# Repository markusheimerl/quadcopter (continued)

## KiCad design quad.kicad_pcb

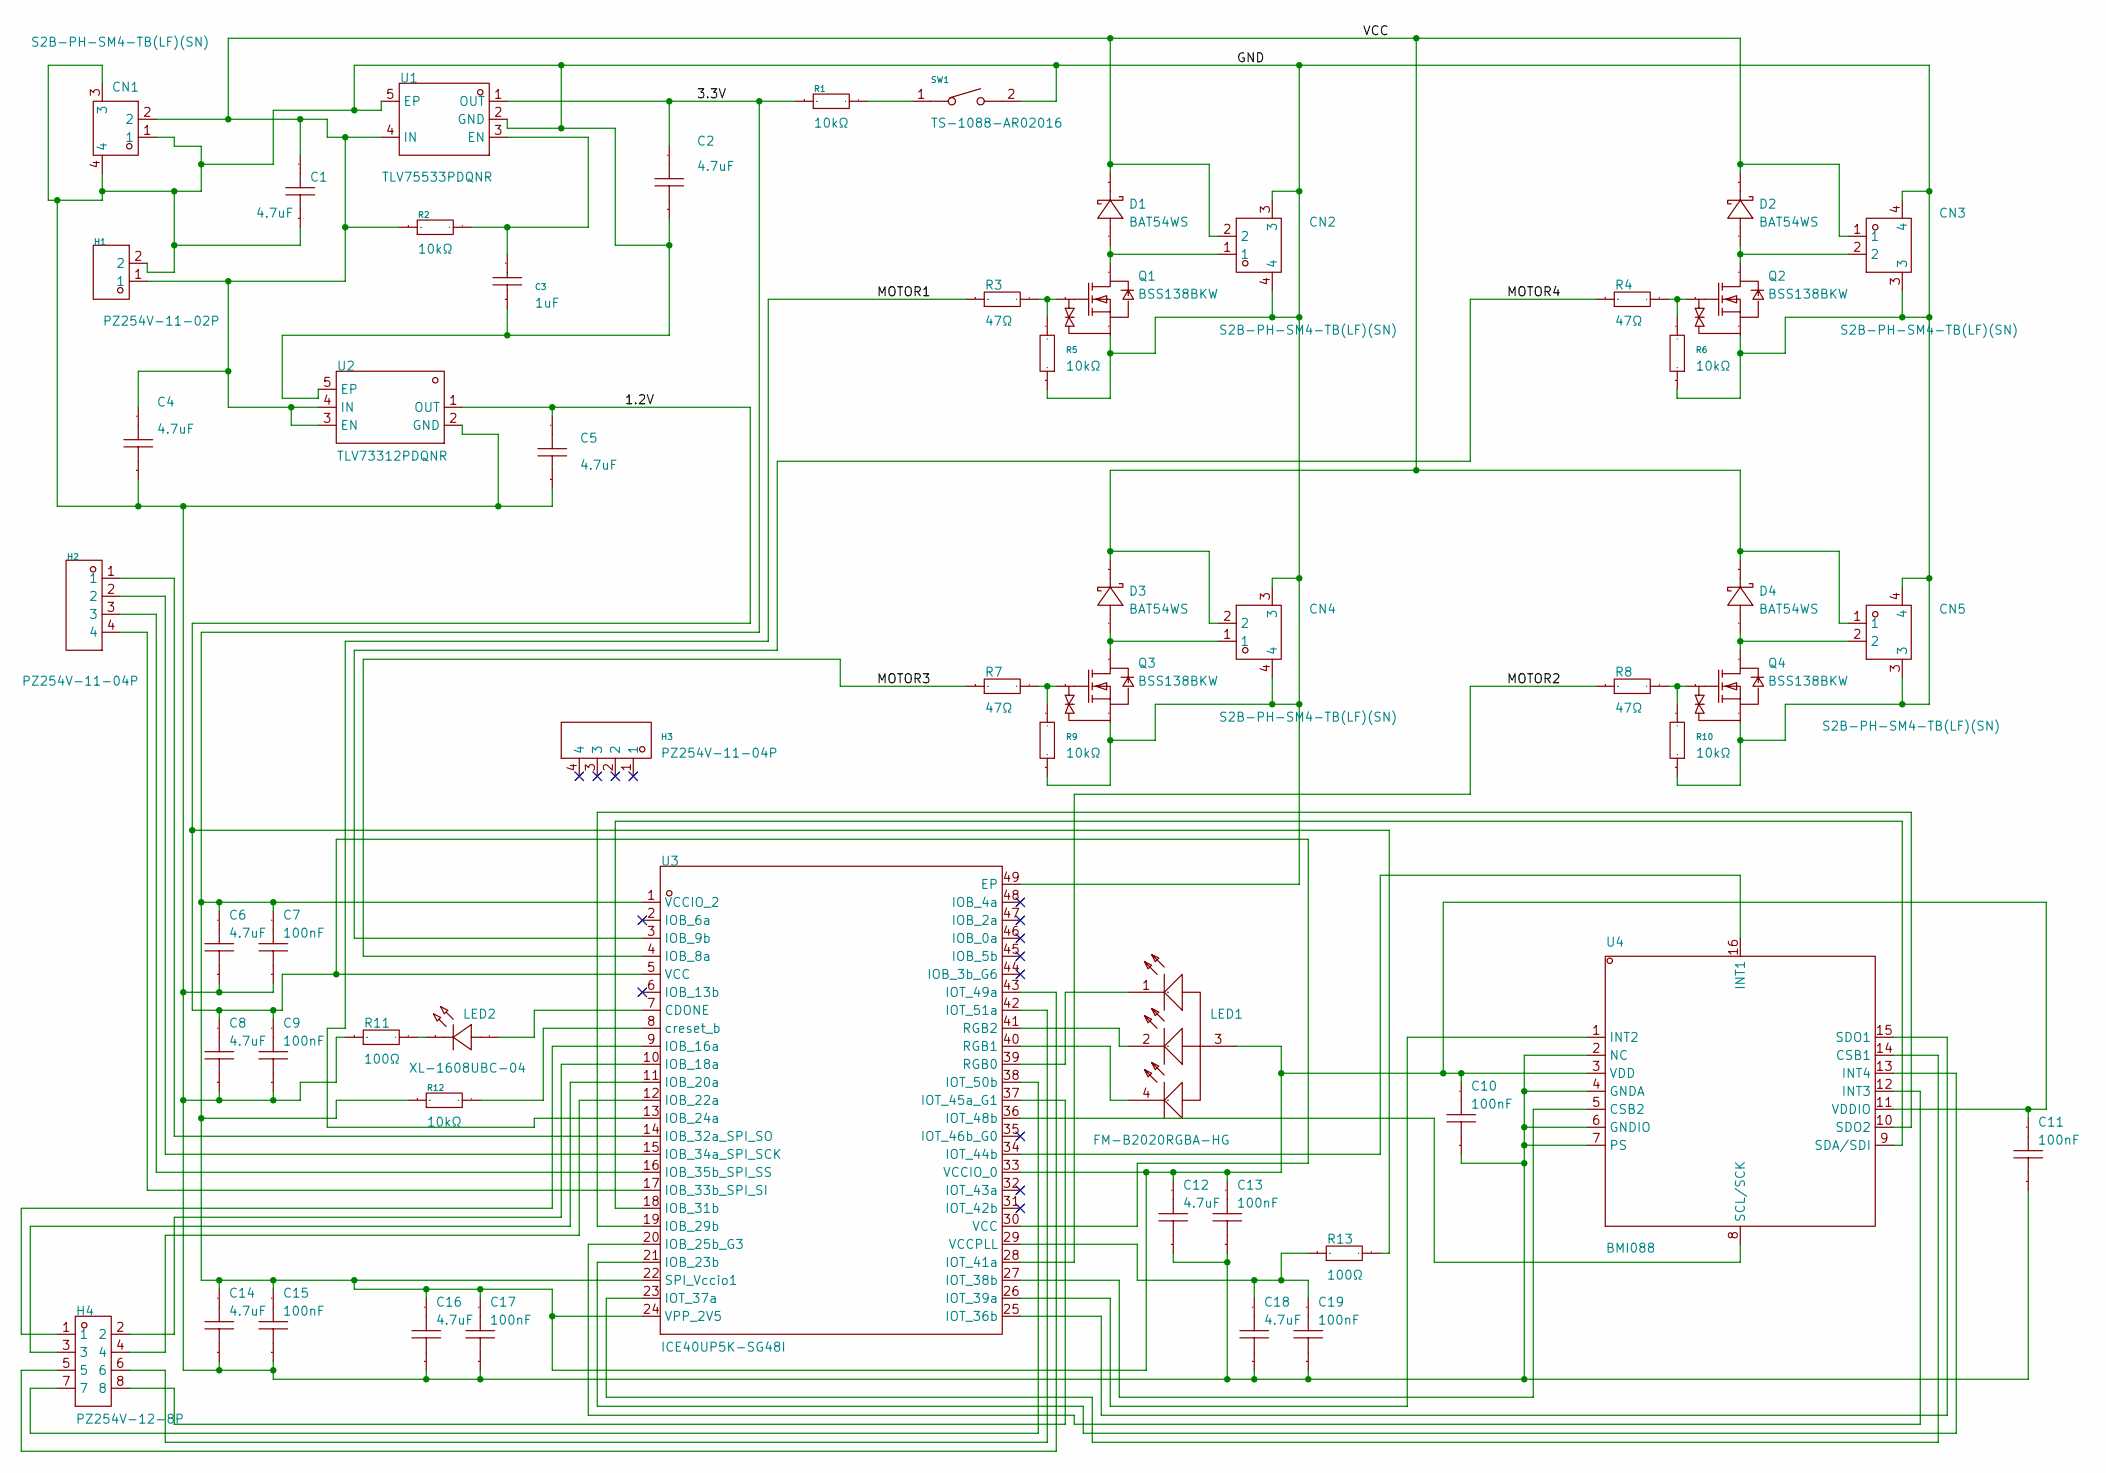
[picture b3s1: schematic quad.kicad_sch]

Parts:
C1, C2, C4, C5, C6, C8, C12, C14, C16, C18: 4.7uF; C0402; Manufacturer Part CL05A475MQ5NRNC; LCSC Part Name 4.7uF ±20% 6.3V
C3: 1uF; C0402; Manufacturer Part CL05A105KO5NNNC; LCSC Part Name 1uF ±10% 16V
C7, C9, C10, C11, C13, C15, C17, C19: 100nF; C0402; Manufacturer Part CL05B104KO5NNNC; LCSC Part Name 100nF ±10% 16V
CN1, CN2, CN3, CN4, CN5: S2B-PH-SM4-TB(LF)(SN); CONN-SMD_P2.00_S2B-PH-SM4-TB-LF-SN; Manufacturer Part S2B-PH-SM4-TB(LF)(SN); LCSC Part Name 1x2P 间距:2mm 卧贴 系列:PH
D1, D2, D3, D4: BAT54WS; SOD-323_L1.7-W1.3-LS2.6-RD-1; Manufacturer Part BAT54WS; LCSC Part Name 电压:30V 电流:200mA
H1: PZ254V-11-02P; HDR-TH_2P-P2.54-V-M; Manufacturer Part PZ254V-11-02P; LCSC Part Name 间距:2.54mm 1x2P 直插 方针
H2, H3: PZ254V-11-04P; HDR-TH_4P-P2.54-V-M; Manufacturer Part PZ254V-11-04P; LCSC Part Name 间距:2.54mm 1x4P 直插 方针
H4: PZ254V-12-8P; HDR-TH_8P-P2.54-V-M-R2-C4-S2.54; Manufacturer Part PZ254V-12-8P; LCSC Part Name 间距:2.54mm 2x4P 直插 方针
LED1: FM-B2020RGBA-HG; LED-SMD_FM-B2020RGBA-HG; Manufacturer Part FM-B2020RGBA-HG; LCSC Part Name FM-B2020RGBA-HG
LED2: XL-1608UBC-04; LED0603-RD_BLUE; Manufacturer Part XL-1608UBC-04; LCSC Part Name XL-1608UBC-04
Q1, Q2, Q3, Q4: BSS138BKW; SOT-323-3_L2.1-W1.3-P1.30-LS2.3-BL; Manufacturer Part BSS138BKW; LCSC Part Name 1个N沟道 耐压:60V 电流:300mA
R1, R2, R5, R6, R9, R10, R12: 10kΩ; R0402; Manufacturer Part 0402WGJ0103TCE; LCSC Part Name 10kΩ ±5% 62.5mW 厚膜电阻
R3, R4, R7, R8: 47Ω; R0402; Manufacturer Part RC0402FR-0747RL; LCSC Part Name 厚膜电阻 47Ω ±1% 62.5mW
R11, R13: 100Ω; R0402; Manufacturer Part RC0402FR-07100RL; LCSC Part Name 厚膜电阻 100Ω ±1% 62.5mW
SW1: TS-1088-AR02016; SW-SMD_L3.9-W3.0-P4.45; Manufacturer Part TS-1088-AR02016; LCSC Part Name 4*3*2mm 立贴 轻触开关
U1: TLV75533PDQNR; X2SON-4_L1.0-W1.0-P0.65-TL-EP; Manufacturer Part TLV75533PDQNR; LCSC Part Name 具有使能功能的 500mA、高 PSRR、低 IQ、低压降稳压器
U2: TLV73312PDQNR; X2SON-4_L1.0-W1.0-P0.65-TL-EP; Manufacturer Part TLV73312PDQNR; LCSC Part Name 具有使能功能的 300mA、低 IQ、低压降无电容稳压器
U3: ICE40UP5K-SG48I; QFN-48_L7.0-W7.0-P0.50-TL-EP5.4-1; Manufacturer Part ICE40UP5K-SG48I; LCSC Part Name ICE40UP5K SG48I
U4: BMI088; LGA-16_L4.5-W3.0-P0.50-BL; Manufacturer Part BMI088; LCSC Part Name BMI088

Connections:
1.2V: C5.2, C8.2, C9.2, R13.2, U2.1 (OUT), U3.5 (VCC), U3.30 (VCC)
3.3V: C2.2, C6.2, C7.2, C10.2, C11.2, C12.2, C13.2, C14.2, C15.2, C16.2, C17.2, LED1.3 (A), R1.1, R12.1, U1.1 (OUT), U3.1 (VCCIO_2), U3.22 (SPI_Vccio1), U3.24 (VPP_2V5), U3.33 (VCCIO_0), U4.3 (VDD), U4.11 (VDDIO)
$1N1853: C3.2, R2.2, U1.3 (EN)
$1N2745: CN3.2, D2.2 (A), Q2.3 (D)
$1N2749: Q2.1 (G), R4.2, R6.2
$1N3427: Q4.1 (G), R8.2, R10.2
$1N3454: CN5.2, D4.2 (A), Q4.3 (D)
$1N4378: CN2.1, D1.2 (A), Q1.3 (D)
$1N4400: Q1.1 (G), R3.2, R5.2
$1N4626: Q3.1 (G), R7.2, R9.2
$1N4630: CN4.1, D3.2 (A), Q3.3 (D)
$1N4970: H2.1, U3.14 (IOB_32a_SPI_SO)
$1N4976: H2.2, U3.15 (IOB_34a_SPI_SCK)
$1N4983: H2.3, U3.16 (IOB_35b_SPI_SS)
$1N5003: H2.4, U3.17 (IOB_33b_SPI_SI)
$1N7555: C18.2, C19.2, R13.1, U3.29 (VCCPLL)
$1N7780: R12.2, U3.8 (creset_b)
$1N8073: LED2.2 (A), U3.7 (CDONE)
$1N8265: LED2.1 (K), R11.2
$1N9704: LED1.2 (K), U3.41 (RGB2)
$1N9752: LED1.4 (K), U3.40 (RGB1)
$1N9758: LED1.1 (K), U3.39 (RGB0)
$1N9959: U3.25 (IOT_36b), U4.15 (SDO1)
$1N9970: U3.34 (IOT_44b), U4.16 (INT1)
$1N11822: H4.1, U3.9 (IOB_16a)
$1N11833: H4.2, U3.10 (IOB_18a)
$1N11847: H4.3, U3.11 (IOB_20a)
$1N11856: H4.4, U3.12 (IOB_22a)
$1N15818: H4.5, U3.43 (IOT_49a)
$1N15829: H4.6, U3.42 (IOT_51a)
$1N15838: H4.7, U3.38 (IOT_50b)
$1N15847: H4.8, U3.37 (IOT_45a_G1)
$1N15910: U3.18 (IOB_31b), U4.9 (SDA/SDI)
$1N15979: U3.19 (IOB_29b), U4.10 (SDO2)
$1N15998: U3.20 (IOB_25b_G3), U4.12 (INT3)
$1N16036: U3.21 (IOB_23b), U4.13 (INT4)
$1N16041: U3.27 (IOT_38b), U4.5 (CSB2)
$1N16063: U3.23 (IOT_37a), U4.14 (CSB1)
$1N16068: U3.26 (IOT_39a), U4.1 (INT2)
$1N16419: U3.36 (IOT_48b), U4.8 (SCL/SCK)
$1N18118: R1.2, SW1.1
GND: C1.1, C2.1, C3.1, C4.1, C5.1, C6.1, C7.1, C8.1, C9.1, C10.1, C11.1, C12.1, C13.1, C14.1, C15.1, C16.1, C17.1, C18.1, C19.1, CN1.1, CN1.3, CN1.4, CN2.3, CN2.4, CN3.3, CN3.4, CN4.3, CN4.4, CN5.3, CN5.4, H1.2, Q1.2 (S), Q2.2 (S), Q3.2 (S), Q4.2 (S), R5.1, R6.1, R9.1, R10.1, R11.1, SW1.2, U1.2 (GND), U1.5 (EP), U2.2 (GND), U2.5 (EP), U3.49 (EP), U4.2 (NC), U4.4 (GNDA), U4.6 (GNDIO), U4.7 (PS)
MOTOR1: R3.1, U3.13 (IOB_24a)
MOTOR2: R8.1, U3.28 (IOT_41a)
MOTOR3: R7.1, U3.4 (IOB_8a)
MOTOR4: R4.1, U3.3 (IOB_9b)
VCC: C1.2, C4.2, CN1.2, CN2.2, CN3.1, CN4.2, CN5.1, D1.1 (K), D2.1 (K), D3.1 (K), D4.1 (K), H1.1, R2.1, U1.4 (IN), U2.3 (EN), U2.4 (IN)

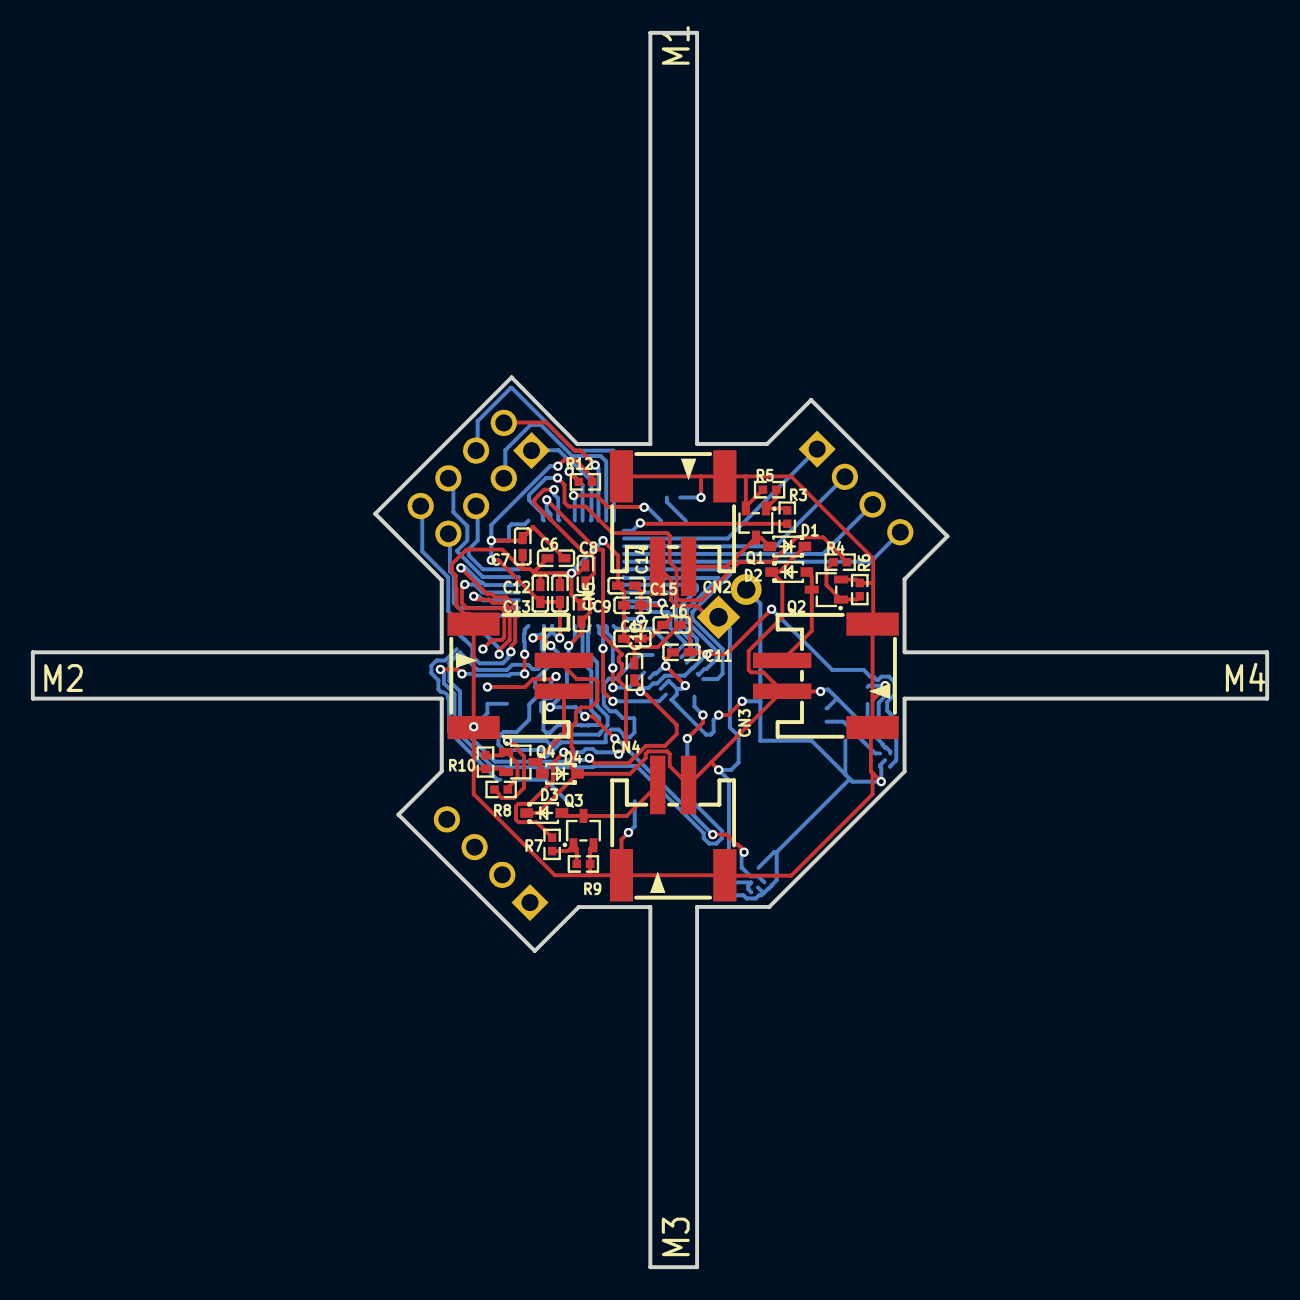
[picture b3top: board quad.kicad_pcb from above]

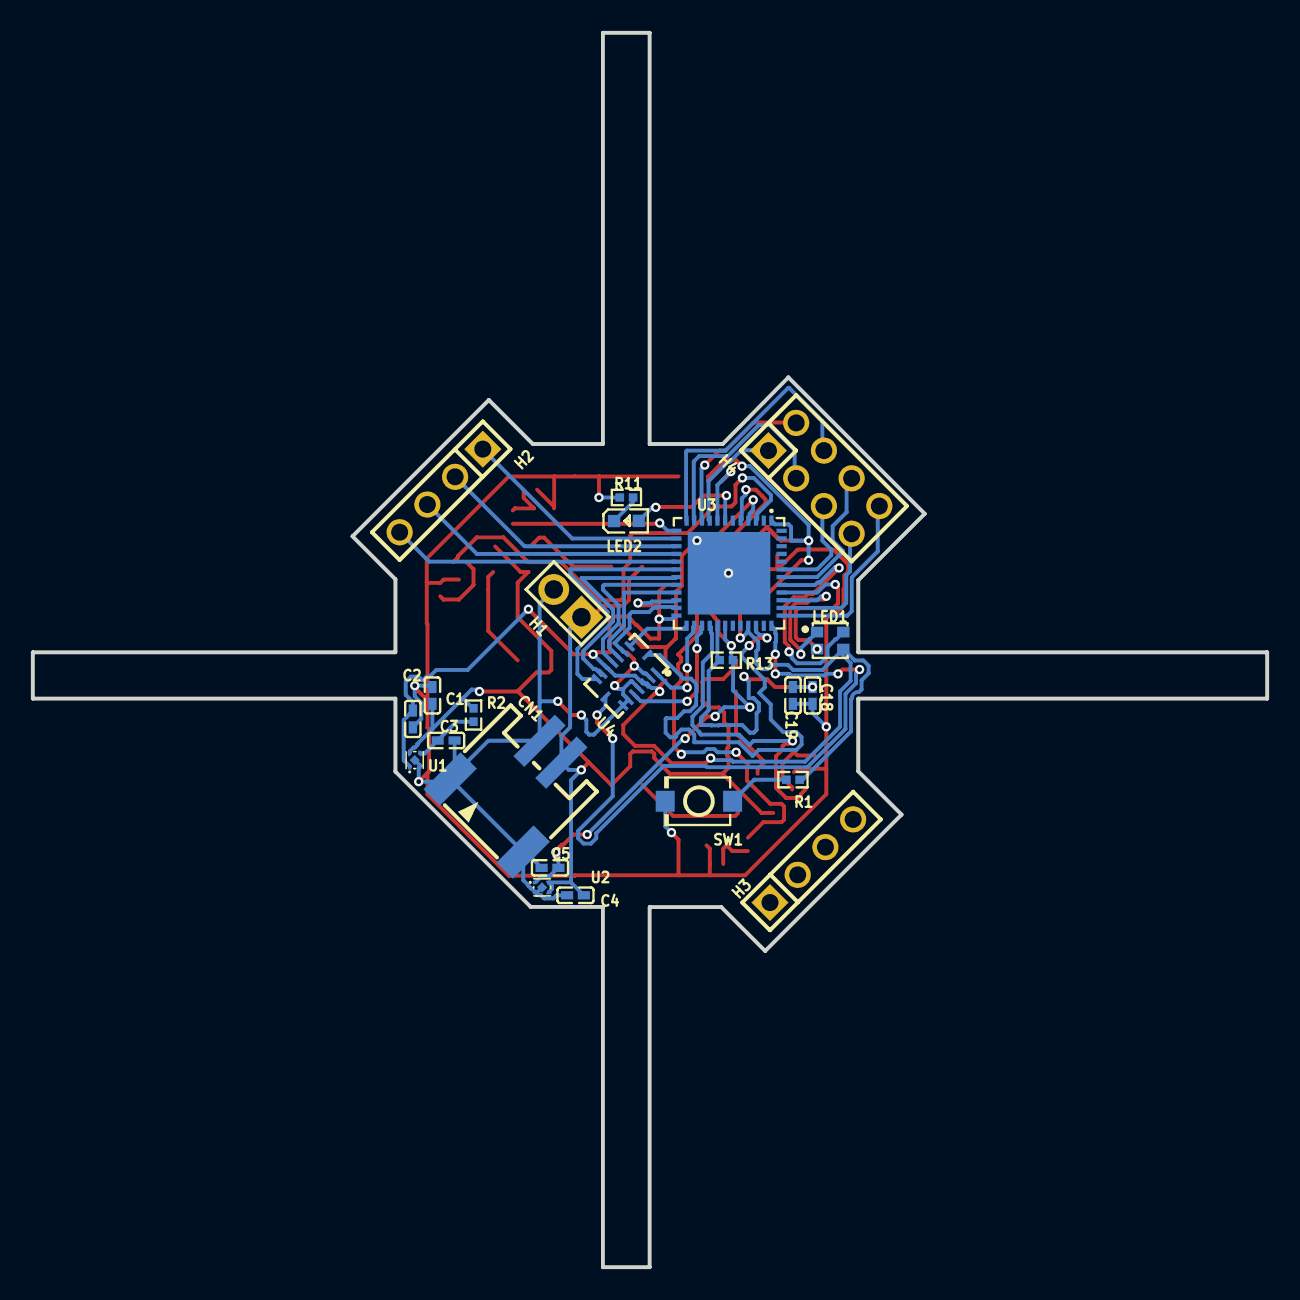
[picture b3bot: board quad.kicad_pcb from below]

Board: 2 copper layers, 80.0 x 80.0 mm, 56 parts (23 on the bottom side), 47 nets.

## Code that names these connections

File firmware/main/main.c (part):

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 * GPIO_OUT_W1T{S,C} / GPIO_ENABLE_W1TS registers are enough.
 */
#define MOTOR0_GPIO     1u
#define MOTOR1_GPIO     2u
#define MOTOR2_GPIO     16u
#define MOTOR3_GPIO     4u
static const uint32_t MOTOR_GPIOS[4] = {
    MOTOR0_GPIO, MOTOR1_GPIO, MOTOR2_GPIO, MOTOR3_GPIO,
};
static const ledc_channel_t MOTOR_LEDC_CH[4] = {
    LEDC_CHANNEL_0, LEDC_CHANNEL_1, LEDC_CHANNEL_2, LEDC_CHANNEL_3,
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
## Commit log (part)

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2024-12-22 Revert "Refactor mesh initialization to create a grid of ground meshes and update rendering logic"
2024-12-22 Add detailed vertices and faces to ground.obj for improved terrain representation
2024-12-22 Prevent drone from going below the ground in dynamics update
2024-12-22 Clarify comment to skip tiny triangles in rasterizer.h
2024-12-22 Implement create_quad function to initialize drone state and refactor simulation code
2024-12-22 Remove unused camera_up parameter from vertex_shader function and adjust main function accordingly
2024-12-22 Simplify mesh transformation code in main function for improved readability
2024-12-22 Optimize main simulation loop by removing redundant frame buffer clearing and clarifying rendering comments
2024-12-22 Update README to describe new MLP controller approach using geometric controller for training
2024-12-22 Enhance README with simulation GIF and adjust quad motor speeds for improved stability
2024-12-23 Add include guards to dynamics.h for improved header safety
2024-12-23 Implement control updates in simulation and adjust loop for step-based iteration
2024-12-23 Remove unused matrix functions from sim.js to streamline code
2024-12-23 Update control gains and scale factors for improved performance
2024-12-23 Fix formatting issue in R_W_d array initialization
2024-12-23 Refactor inertia matrix calculations for improved clarity and performance
2024-12-23 Refactor matrix and vector operations to use double precision for improved accuracy
2024-12-23 Refactor floating-point constants and initializations to use double precision for consistency
2024-12-24 Implement orthonormalization of rotation matrix for improved stability in drone physics
2024-12-24 Update time step definition for improved simulation accuracy
2024-12-26 Add quad.h for drone state and control implementation
2024-12-26 Refactor drone control logic for improved clarity and organization
2024-12-26 Revert "Refactor drone physics update for improved clarity and efficiency"
2024-12-26 Refactor update_drone_control for improved readability and organization
2024-12-27 Update yaw initialization and increase simulation steps for improved accuracy
2024-12-27 Add RENDER flag support for optional visualization in simulation
2024-12-27 Add logging functionality for drone simulation data and initialize omega_next
2024-12-27 Refactor simulation loop to include stability check and increase maximum steps
2024-12-27 Reduce stability threshold for angular velocity check in simulation
2024-12-27 Refactor rotation matrix update and adjust stability threshold for angular velocity check
2024-12-27 Update GitHub Actions workflow to enhance simulation data processing and release handling
2024-12-28 Refactor simulation control logic to improve stability checks and enhance logging functionality
2024-12-28 Refactor drone physics update to accept variable time step and improve simulation timing control
2024-12-28 Reorder include directives for conditional compilation of rendering components
2024-12-28 Refactor simulation workflow to enhance error handling and streamline data upload process
2024-12-28 Update simulation data pipeline to use Ubuntu 24.04 for improved compatibility
2024-12-28 Refactor simulation data pipeline to streamline data processing and upload steps
2024-12-28 Add command-line argument support for max simulation steps
2024-12-28 Add input for simulation size in workflow dispatch
2024-12-29 Refactor simulation loop to improve control flow and remove unnecessary variables
2024-12-29 Update subproject commit reference in rasterizer
2025-01-05 Reduce maximum simulation steps from 5000 to 50 for improved performance and adjust logging frequency accordingly
2025-01-05 Add CSV files to .gitignore to prevent tracking of simulation output data
2025-01-05 Update clean target in Makefile to remove control data CSV files
2025-01-06 Refactor drone physics parameters and improve simulation divergence checks
2025-01-07 Refactor drone control logic to improve velocity error calculation and update logging format
2025-01-07 Clamp rotor speeds to defined limits and refine divergence conditions for improved simulation accuracy
2025-01-08 Refactor drone control logic to improve position tracking and stability; update logging format for clarity
2025-01-08 Reset drone state variables and adjust control constants for improved simulation dynamics
2025-01-08 Add noise modeling for sensor readings; initialize bias variables for accelerometer and gyroscope
2025-01-08 Add wind force modeling and update control constants for improved simulation accuracy
2025-01-10 Remove commented-out wind target adjustment logic in drone physics update
2025-01-11 Add reward calculation to simulation logging and refine position achievement criteria
2025-01-11 Update Makefile and simulation logging to track state data and implement discounted rewards
2025-01-13 Remove outdated drone control logic to streamline update process
2025-01-13 Refactor simulation initialization to conditionally allocate resources based on render flag; improve memory management in free_sim function
2025-01-13 Update Makefile to streamline build commands for render and log targets
2025-01-13 Remove unused matrix operations and helper functions in vmath.h to improve code clarity and maintainability
2025-01-13 Refactor control input calculations and streamline target generation output for improved readability
2025-01-14 Update drone simulation image in README for improved representation
2025-01-16 Update init_sim function to accept a prefix for mesh paths
2025-01-18 Remove OpenBLAS dependency from Makefile and simplify crossVec3f implementation
2025-01-18 Refactor quad dynamics calculations to streamline thrust and torque computations; combine related operations for improved clarity and performance
2025-01-23 Remove drone kicad files
2025-01-23 Update images in README.md to use new URLs for drone components
2025-01-25 Add new KiCad library files for quad components and footprints
2025-01-25 Add initial raytracer implementation with Makefile and basic structure
2025-01-25 Update Makefile to clean up output files
2025-01-26 Update Makefile with additional flags and libraries and integrated raytracer
2025-01-26 Update quadcopter rendering to apply scale, rotation, and order.
2025-01-26 Updated raytracer submodule commit
2025-01-27 Implement camera struct and refactor render function to use camera parameters
2025-01-27 Refactor rendering system: introduce Scene struct for better management of meshes and camera, and update main function to utilize new scene handling
2025-01-27 Add support for vertex normals in mesh loading: update create_mesh function to parse and store normals from OBJ files, and modify Triangle struct to include normal data
2025-01-27 Update camera and light direction in scene setup: adjust camera position and normalize light direction vector
2025-01-27 Add frame-based animation support: modify scene structure to handle multiple frames, update rendering loop for animated meshes, and implement WebP animation saving
2025-01-27 Update clean target in Makefile to remove rendering output files
2025-01-27 Set WebP quality to maximum for improved image output
2025-01-27 Add vmath.h for vector and matrix operations
2025-01-27 Adjust scene scaling factor from 1.0 to 0.9 for improved rendering dynamics
2025-01-27 Implement normal transformation for mesh rendering and add matrix transpose function
2025-01-27 Update scene scaling factor to 0.9 for improved rendering dynamics
2025-01-27 Refactor simulation code: replace sim.c with main.c, update Makefile, and modify .gitignore
2025-01-27 Enhance simulation: add random yaw initialization and update control input for quadcopter
2025-01-27 Update .gitignore to include flight webp files and adjust raytracer scene parameter
2025-02-08 Add usage instructions to README and ensure animation image is displayed
2025-02-09 Refactor Makefile: simplify target definitions and streamline build commands
2025-02-09 Refactor update_quad function: enhance comments for clarity, improve state evolution calculations, and ensure orthonormalization of rotation matrix
2025-02-09 Add symbolic dynamics calculations for rotorcraft: define state variables, thrust, torques, and gradients
2025-02-10 Refactor main simulation loop: consolidate target position and yaw into a single array, update scene frame count based on simulation time, and improve readability of control updates and rendering log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
2025-02-12 Remove sympy implementation of quadrotor dynamics from syms.py
2025-02-13 Refactor matrix initialization for clarity and consistency in vmath.h
2025-02-19 Revert "Refactor simulation to calculate yaw dynamically and adjust simulation duration"
2025-02-19 Add bias and scale factors for accelerometer and gyroscope measurements in Quad structure
2025-02-20 Refactor control_quad function to accept position, velocity, and inertia parameters; update simulation to use new function signature
2025-02-20 Refactor quad initialization by replacing reset_quad function with create_quad; update main simulation logic to accommodate new structure
2025-03-01 Cleanup: Add mesh destruction calls in main and remove redundant destruction loop in destroy_scene
2025-03-06 Add yaw parameter to create_quad function and update initialization in main simulation
2025-03-07 Refactor drone simulation: streamline target position calculation, enhance randomization, and improve logging for clarity
2025-03-07 Revert "Enhance quad simulation: add magnetometer measurements and bias handling, update estimator to include yaw correction from magnetometer data"
2025-03-08 Update magnetometer vector in quad simulation; improve logging for drone and target positions
2025-03-08 Revert "Refactor quad simulation: remove state estimator structure and related logic, update control function to use direct quad values"
2025-03-11 Revert "Enhance quad simulation: modify create_quad function to accept sensor scale factors; update update_quad_states to use provided noise inputs for bias and measurement noise"
2025-06-11 Update repository to blcd version
2025-07-19 Add new project files for quadcopter designs and update README to remove old images
2025-07-19 Update LICENSE
2025-07-23 Add new .epro file and PCB image for FPGA design
2025-07-23 Comment out Quad Schematic image in README.md
2025-07-23 Add new BLDC .epro file and PCB image
2025-07-24 Add new FPGA .epro file and corresponding PCB image
2025-07-25 Add new camera .epro file and corresponding PCB and schematic images
2025-07-28 Complete modular refactoring - improved separation of concerns and project structure
2025-07-28 Simplify Makefile to match original structure - remove complex build logic and static linking
2025-07-29 Add updated FPGA .epro file and corresponding PCB image
2025-08-04 Restructure project with individual Makefile targets for parallel compilation
2025-08-04 Optimize default thread count to 2 for best performance
2025-08-12 Refactor Makefile and README for OpenMP support; enhance scene creation and rendering with parallelization
2025-08-20 Update FPGA files and PCB image to version 2025_08_20
2025-08-24 Fix LED PCB image link in README.md
2025-08-26 Add new USB2UART files and PCB/schematic images for version 2025_08_26
2025-09-12 Replace obsolete LED files with new versions and update README.md references
2025-10-06 Refactor Makefile and update mesh paths in sim.c to use new asset directory structure
2025-10-26 Update project description in README
2025-12-07 Refactor quad and simulation code: remove state estimator and related measurements from main simulation loop
2025-12-11 Add Enzyme autodiff support and optimize controller gains in simulation
2026-03-07 Remove raytracer submodule
2026-03-07 Adjust scene resolution and parameters for improved simulation performance
2026-03-07 Add section on autodifferentiation using Enzyme in README
2026-03-08 Update project name and description in README
2026-05-23 Add initial firmware files for quadcopter project, including CMake configuration, main application, and README documentation
2026-05-23 Enhance firmware: add BLE support and motor control commands, update CMake configuration, and optimize SDK settings
